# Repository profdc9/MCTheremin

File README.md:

This is a theremin based on the "Bluepill" devboard with a STM32F103C8T6 microcontroller.
This material is copyrighted by Daniel Marks (KW4TI) and licensed under
the Creative Commons License CC-BY-SA 4.0.  Software is copyrighted using the zlib
open-source license.

It consists of three parts: 

MCTheremin directory - the stm32duino project

board - the PCB board in Kicad of the theremin.

genwaves - little octave script to generate the waveform data

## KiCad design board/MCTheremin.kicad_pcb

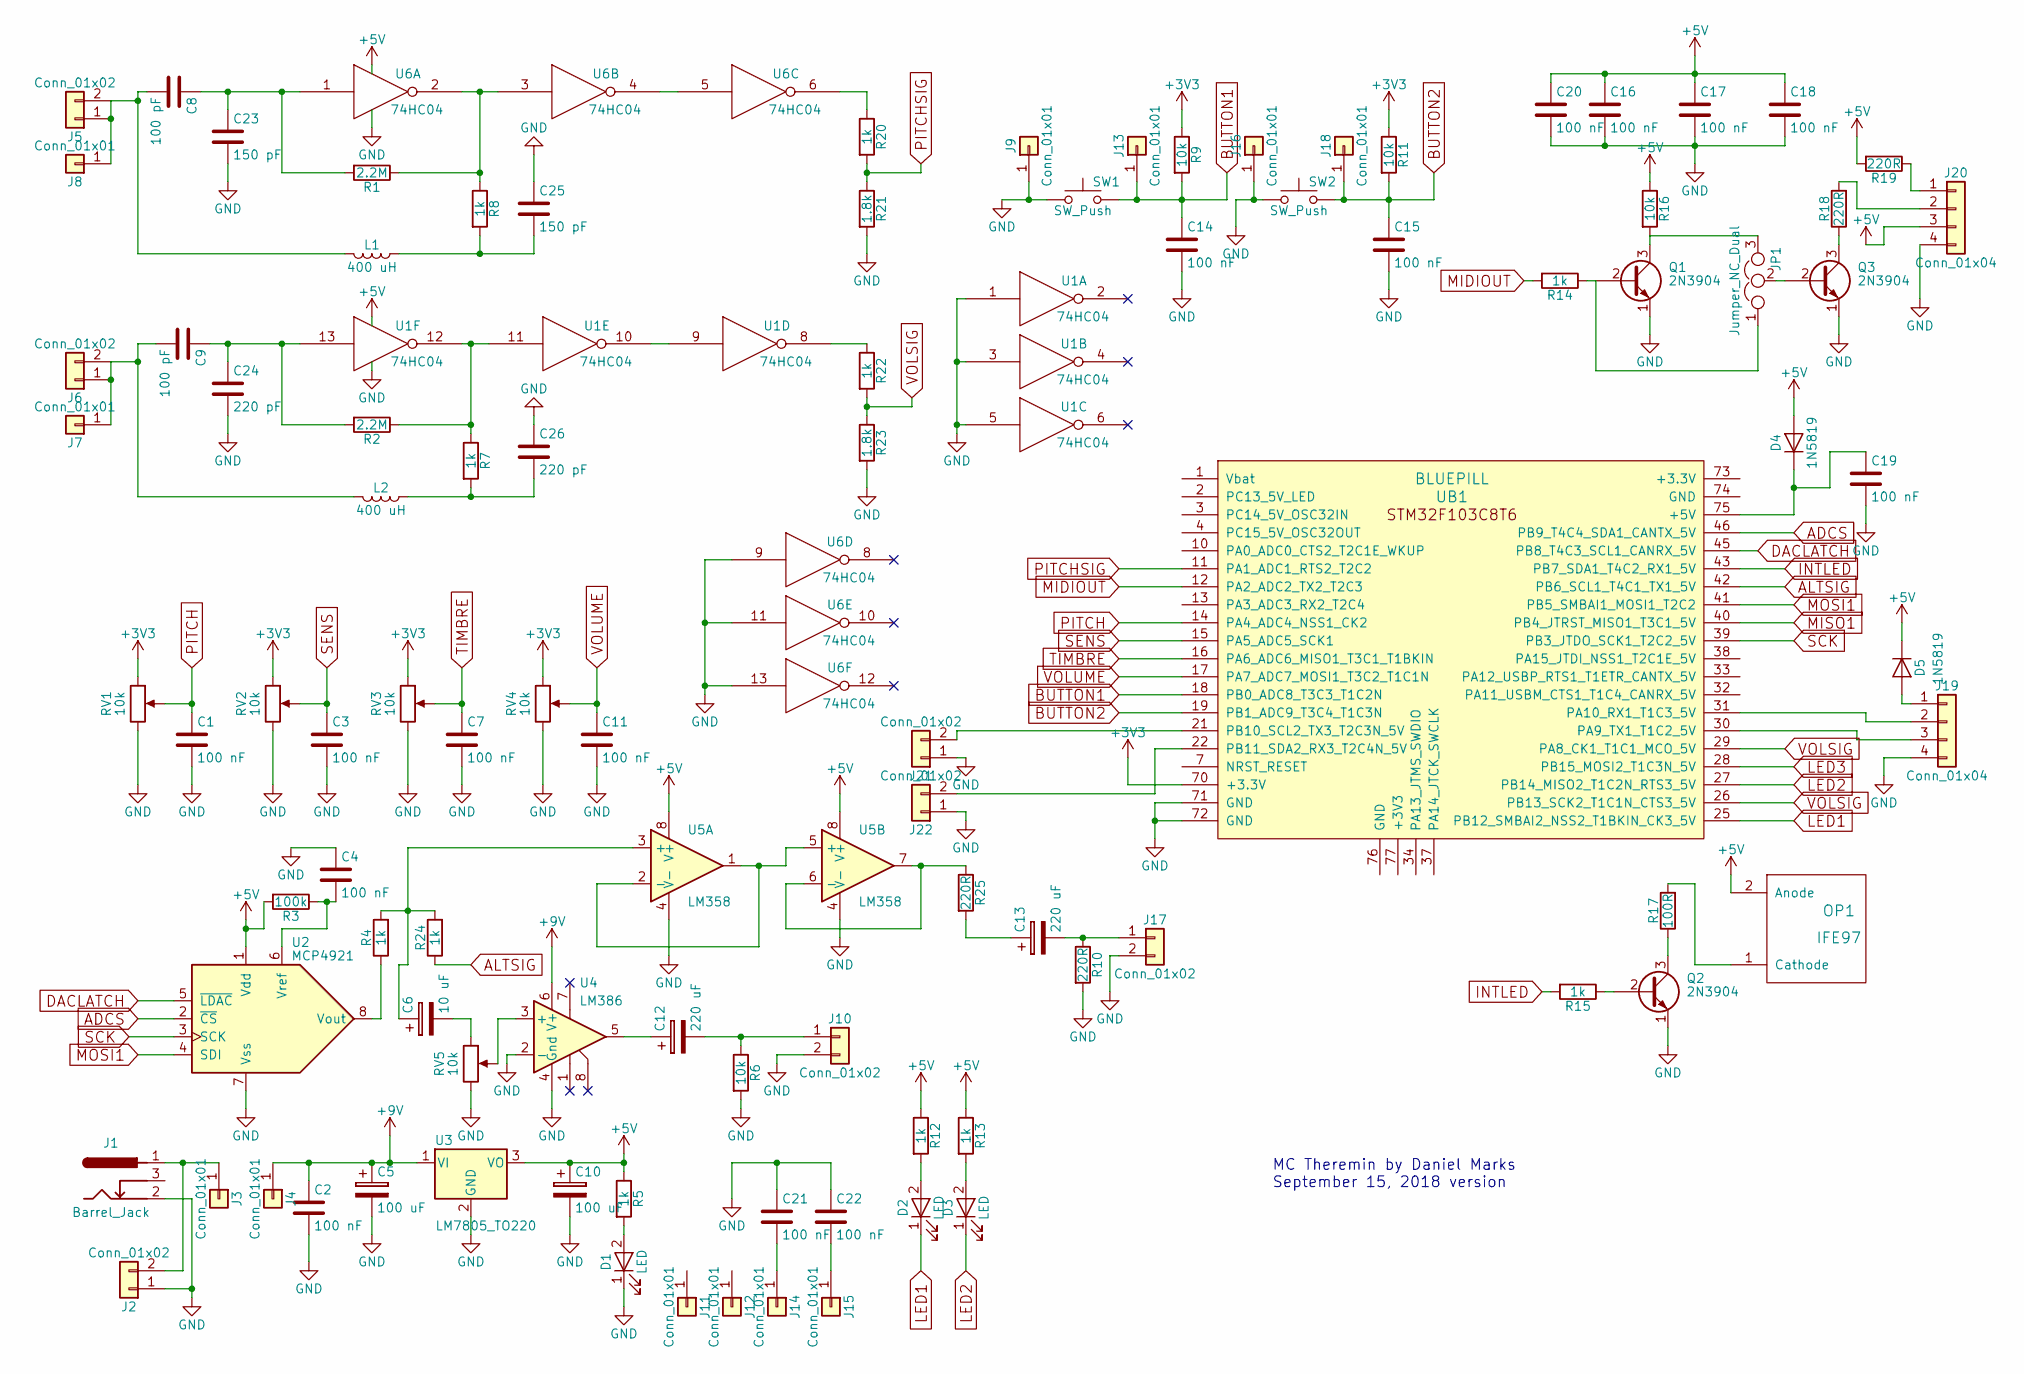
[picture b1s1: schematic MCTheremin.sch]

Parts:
C1, C2, C3, C4, C7, C11, C14, C15, C16, C17, C18, C19, C20, C21, C22: 100 nF; C_Disc_D5.0mm_W2.5mm_P5.00mm
C5, C10: 100 uF; CP_Radial_D7.5mm_P2.50mm
C6: 10 uF; CP_Radial_D7.5mm_P2.50mm
C8, C9: 100 pF; C_Disc_D5.0mm_W2.5mm_P5.00mm
C12, C13: 220 uF; CP_Radial_D7.5mm_P2.50mm
C23, C25: 150 pF; C_Disc_D5.0mm_W2.5mm_P5.00mm
C24, C26: 220 pF; C_Disc_D5.0mm_W2.5mm_P5.00mm
D1, D2, D3: LED; LED_D5.0mm
D4, D5: 1N5819; D_DO-41_SOD81_P7.62mm_Horizontal
J1: Barrel_Jack; BARREL_JACK
J2, J5, J6, J10, J17, J21, J22: Conn_01x02; TerminalBlock_bornier-2_P5.08mm
J3, J4, J7, J8, J9, J11, J12, J13, J14, J15, J16, J18: Conn_01x01; 1pin
J19, J20: Conn_01x04; Pin_Header_Straight_1x04_Pitch2.54mm
JP1: Jumper_NC_Dual; Pin_Header_Straight_1x03_Pitch2.54mm
L1, L2: 400 uH; L_Axial_L7.0mm_D3.3mm_P12.70mm_Horizontal_Fastron_MICC
OP1: IFE97
Q1, Q2, Q3: 2N3904; TO-92_Molded_Narrow
R1, R2: 2.2M; R_Axial_DIN0207_L6.3mm_D2.5mm_P7.62mm_Horizontal
R3: 100k; R_Axial_DIN0207_L6.3mm_D2.5mm_P7.62mm_Horizontal
R4, R5, R7, R8, R12, R13, R14, R15, R20, R22, R24: 1k; R_Axial_DIN0207_L6.3mm_D2.5mm_P7.62mm_Horizontal
R6, R9, R11, R16: 10k; R_Axial_DIN0207_L6.3mm_D2.5mm_P7.62mm_Horizontal
R10, R18, R19, R25: 220R; R_Axial_DIN0207_L6.3mm_D2.5mm_P7.62mm_Horizontal
R17: 100R; R_Axial_DIN0207_L6.3mm_D2.5mm_P7.62mm_Horizontal
R21, R23: 1.8k; R_Axial_DIN0207_L6.3mm_D2.5mm_P7.62mm_Horizontal
RV1, RV2, RV3, RV4, RV5: 10k; Potentiometer_WirePads
SW1, SW2: SW_Push; SW_PUSH_6mm_h4.3mm
U1, U6: 74HC04; DIP-14_W7.62mm_Socket
U2: MCP4921; DIP-8_W7.62mm_Socket
U3: LM7805_TO220; TO-220-3_Vertical
U4: LM386; DIP-8_W7.62mm_Socket
U5: LM358; DIP-8_W7.62mm_Socket
UB1: BLUEPILL

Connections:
+3V3: R9.1, R11.1, RV1.1, RV2.1, RV3.1, RV4.1, UB1.70 (+3.3V)
+5V: C10.1, C16.1, C17.1, C18.1, C20.1, D4.2 (A), D5.1 (K), J20.3, OP1.2 (Anode), R3.2, R5.1, R12.1, R13.1, R16.1, R19.2, U1.14 (VCC), U2.1 (Vdd), U3.3 (VO), U5.8 (V+), U6.14 (VCC)
+9V: C2.1, C5.1, J4.1, U3.1 (VI), U4.6 (V+)
ADCS: U2.2 (~CS), UB1.46 (PB9_T4C4_SDA1_CANTX_5V)
ALTSIG: R24.1, UB1.42 (PB6_SCL1_T4C1_TX1_5V)
BUTTON1: C14.1, J13.1, R9.2, SW1.2, UB1.18 (PB0_ADC8_T3C3_T1C2N)
BUTTON2: C15.1, J18.1, R11.2, SW2.2, UB1.19 (PB1_ADC9_T3C4_T1C3N)
DACLATCH: U2.5 (~LDAC), UB1.45 (PB8_T4C3_SCL1_CANRX_5V)
GND: C1.2, C2.2, C3.2, C4.1, C5.2, C7.2, C10.2, C11.2, C14.2, C15.2, C16.2, C17.2, C18.2, C19.2, C20.2, C21.1, C22.1, C23.2, C24.2, C25.1, C26.1, D1.1 (K), J1.2, J2.1, J9.1, J10.2, J16.1, J17.2, J19.4, J20.4, J21.1, J22.1, Q1.1 (E), Q2.1 (E), Q3.1 (E), R6.2, R10.2, R21.2, R23.2, RV1.3, RV2.3, RV3.3, RV4.3, RV5.3, SW1.1, SW2.1, U1.1, U1.3, U1.5, U1.7 (GND), U2.7 (Vss), U3.2 (GND), U4.2 (-), U4.4 (Gnd), U5.4 (V-), U6.7 (GND), U6.9, U6.11, U6.13, UB1.71 (GND), UB1.72 (GND)
INTLED: R15.2, UB1.43 (PB7_SDA1_T4C2_RX1_5V)
LED1: D2.1 (K), UB1.25 (PB12_SMBAI2_NSS2_T1BKIN_CK3_5V)
LED2: D3.1 (K), UB1.27 (PB14_MISO2_T1C2N_RTS3_5V)
MIDIOUT: R14.2, UB1.12 (PA2_ADC2_TX2_T2C3)
MOSI1: U2.4 (SDI), UB1.41 (PB5_SMBAI1_MOSI1_T2C2)
unnamed: C4.2, R3.1, U2.6 (Vref)
unnamed: C6.1, R4.2, R24.2, U5.3 (+)
unnamed: C6.2, RV5.1
unnamed: C8.2, J5.1, J5.2, J8.1, L1.2
unnamed: C9.2, J6.1, J6.2, J7.1, L2.2
unnamed: C12.1, U4.5
unnamed: C12.2, J10.1, R6.1
unnamed: C13.1, R25.2
unnamed: C13.2, J17.1, R10.1
unnamed: C19.1, D4.1 (K), UB1.75 (+5V)
unnamed: C21.2, J14.1
unnamed: C22.2, J15.1
unnamed: C8.1, C23.1, R1.2, U6.1
unnamed: C9.1, C24.1, R2.2, U1.13
unnamed: C25.2, L1.1, R8.2
unnamed: C26.2, L2.1, R7.2
unnamed: D1.2 (A), R5.2
unnamed: D2.2 (A), R12.2
unnamed: D3.2 (A), R13.2
unnamed: D5.2 (A), J19.1
unnamed: J1.1, J2.2, J3.1
unnamed: J19.2, UB1.31 (PA10_RX1_T1C3_5V)
unnamed: J19.3, UB1.30 (PA9_TX1_T1C2_5V)
unnamed: J20.1, R19.1
unnamed: J20.2, R18.2
unnamed: J21.2, UB1.21 (PB10_SCL2_TX3_T2C3N_5V)
unnamed: J22.2, UB1.22 (PB11_SDA2_RX3_T2C4N_5V)
unnamed: JP1.1, Q1.2 (B), R14.1
unnamed: JP1.2, Q3.2 (B)
unnamed: JP1.3, Q1.3 (C), R16.2
unnamed: OP1.1 (Cathode), R17.2
unnamed: Q2.2 (B), R15.1
unnamed: Q2.3 (C), R17.1
unnamed: Q3.3 (C), R18.1
unnamed: R1.1, R8.1, U6.2, U6.3
unnamed: R2.1, R7.1, U1.11, U1.12
unnamed: R4.1, U2.8 (Vout)
unnamed: R20.1, U6.6
unnamed: R22.1, U1.8
unnamed: R25.1, U5.6 (-), U5.7
unnamed: RV5.2, U4.3 (+)
unnamed: U1.9, U1.10
unnamed: U5.1, U5.2 (-), U5.5 (+)
unnamed: U6.4, U6.5
PITCH: C1.1, RV1.2, UB1.14 (PA4_ADC4_NSS1_CK2)
PITCHSIG: R20.2, R21.1, UB1.11 (PA1_ADC1_RTS2_T2C2)
SCK: U2.3 (SCK), UB1.39 (PB3_JTDO_SCK1_T2C2_5V)
SENS: C3.1, RV2.2, UB1.15 (PA5_ADC5_SCK1)
TIMBRE: C7.1, RV3.2, UB1.16 (PA6_ADC6_MISO1_T3C1_T1BKIN)
VOLSIG: R22.2, R23.1, UB1.26 (PB13_SCK2_T1C1N_CTS3_5V), UB1.29 (PA8_CK1_T1C1_MCO_5V)
VOLUME: C11.1, RV4.2, UB1.17 (PA7_ADC7_MOSI1_T3C2_T1C1N)

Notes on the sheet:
MC Theremin by Daniel Marks September 15, 2018 version

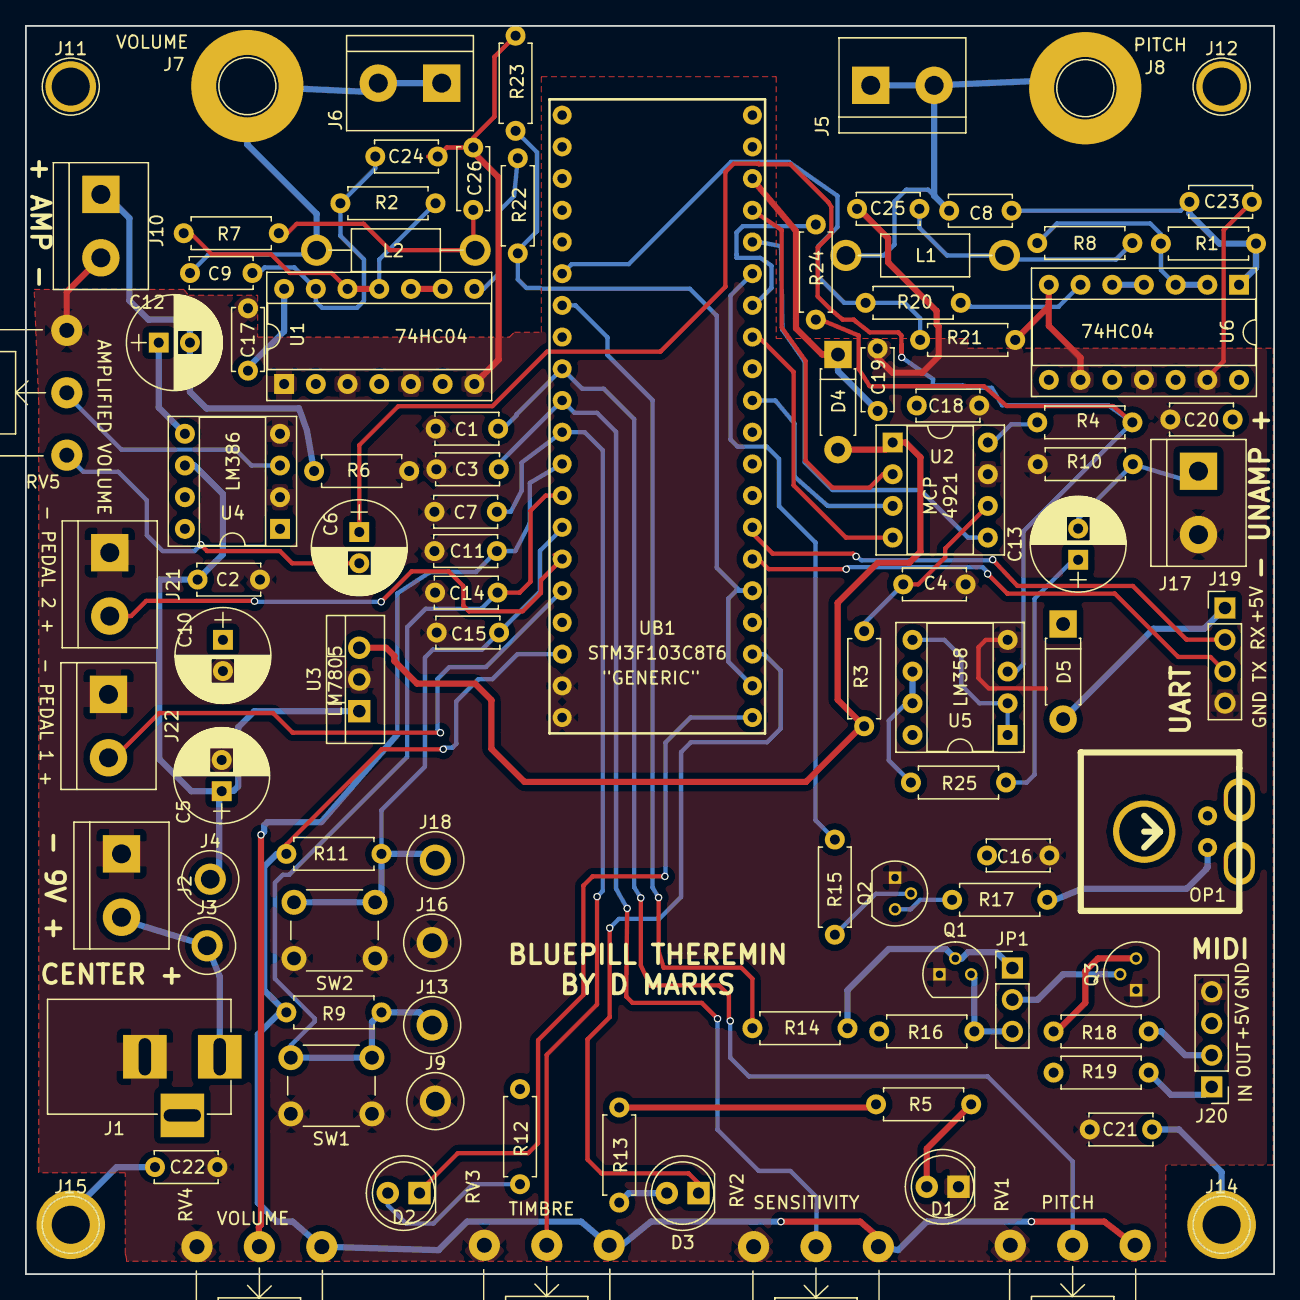
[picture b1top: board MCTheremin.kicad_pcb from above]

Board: 2 copper layers, 100.0 x 100.0 mm, 99 parts (0 on the bottom side), 65 nets.

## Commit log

2018-09-17 Pre LC
2018-09-23 Changed to LC oscillator - removed copper fill from under oscillator
2018-10-07 First working MCTheremin with LC oscillators
2018-10-27 Redid the frequency counter to get rid of nasty warble
2019-01-12 Accidental connection in LM358
